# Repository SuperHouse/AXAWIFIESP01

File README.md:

AXA Electric Window Motor WiFi Controller (ESP-01)
===================================================
Copyright 2017 SuperHouse Automation Pty Ltd  www.superhouse.tv  

Add-in board for AXA domestic electric window mechanisms, to fit into
the battery compartment in place of the AA cells that are normally
installed. Uses an ESP8266 to connect to WiFi, and controls the AXA
window motor using LINbus.

More information is available on the project page at:

  http://www.superhouse.tv/axawifi

INSTALLATION
------------
The design is saved as an EAGLE project. EAGLE PCB design software is
available from www.cadsoftusa.com free for non-commercial use. To use
this project download it and place the directory containing these files
into the "eagle" directory on your computer. Then open EAGLE and
navigate to the projects listing.

DISTRIBUTION
------------
The specific terms of distribution of this project are governed by the
license referenced below.

LICENSE
-------
Licensed under the TAPR Open Hardware License (www.tapr.org/OHL).
The "license" folder within this repository also contains a copy of
this license in plain text format.

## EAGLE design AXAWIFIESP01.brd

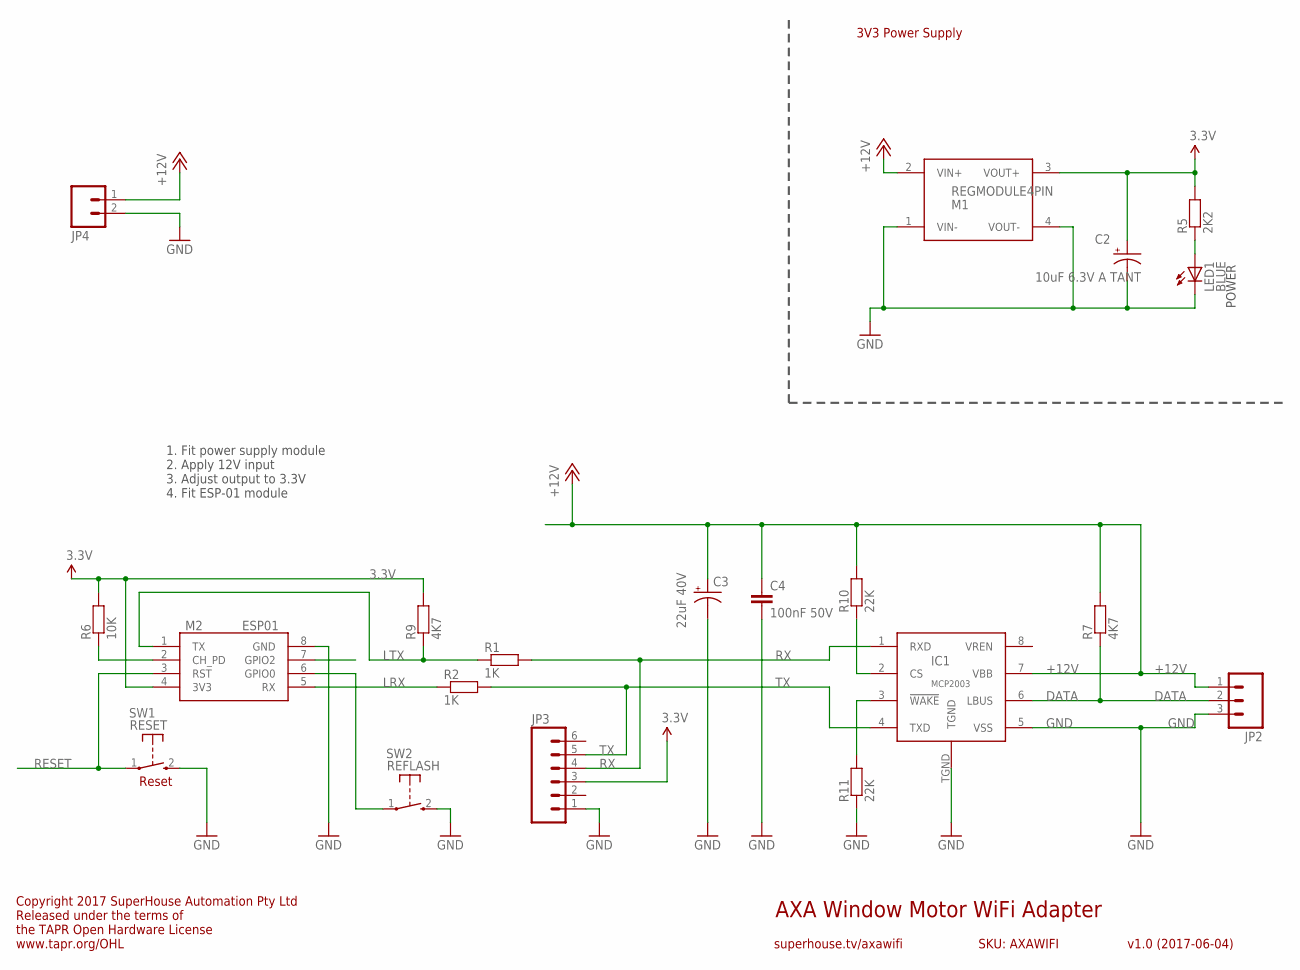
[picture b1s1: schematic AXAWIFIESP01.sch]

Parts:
C2: 10uF 6.3V A TANT; EIA3216
C3: 22uF 40V; PANASONIC_C
C4: 100nF 50V; C0603
IC1: MCP2003; SOIC8T
JP2: M03PTH; 1X03
JP3: M06SIP; 1X06
JP4: M02-SCREW-3.5MM; SCREWTERMINAL-3.5MM-2
LED1: BLUE; LED-0603
M1: REGMODULE4PIN
M2: ESP01
R1, R2: 1K; R0603
R5: 2K2; R0603
R6: 10K; R0603
R7, R9: 4K7; R0603
R10, R11: 22K; R0603
SW1: RESET; TACTILE_SMT_3X4X2
SW2: REFLASH; TACTILE_SMT_3X4X2

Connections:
3.3V: C2.A (+), JP3.3, M1.3 (VOUT+), M2.4 (3V3), R5.2, R6.2, R9.2
+12V: C3.+, C4.1, IC1.7 (VBB), JP2.1, JP4.1, M1.2 (VIN+), R7.2, R10.2
DATA: IC1.6 (LBUS), JP2.2, R7.1
GND: C2.C (-), C3.-, C4.2, IC1.5 (VSS), IC1.TGND, JP2.3, JP3.1, JP4.2, LED1.C, M1.1 (VIN-), M1.4 (VOUT-), M2.8 (GND), R11.1, SW1.2 (S), SW2.2 (S)
LRX: M2.5 (RX), R2.1
LTX: M2.1 (TX), R1.1, R9.1
unnamed: M2.6 (GPIO0), SW2.1
unnamed: M2.2 (CH_PD), R6.1
unnamed: IC1.2 (CS), R10.1
unnamed: IC1.3 (!WAKE), R11.2
unnamed: LED1.A, R5.1
RESET: M2.3 (RST), SW1.1
RX: IC1.1 (RXD), JP3.4, R1.2
TX: IC1.4 (TXD), JP3.5, R2.2

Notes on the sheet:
AXA Window Motor WiFi Adapter
v1.0 (2017-06-04)
superhouse.tv/axawifi
SKU: AXAWIFI
Reset
Copyright 2017 SuperHouse Automation Pty Ltd Released under the terms of the TAPR Open Hardware License www.tapr.org/OHL
POWER
3V3 Power Supply
1. Fit power supply module 2. Apply 12V input 3. Adjust output to 3.3V 4. Fit ESP-01 module

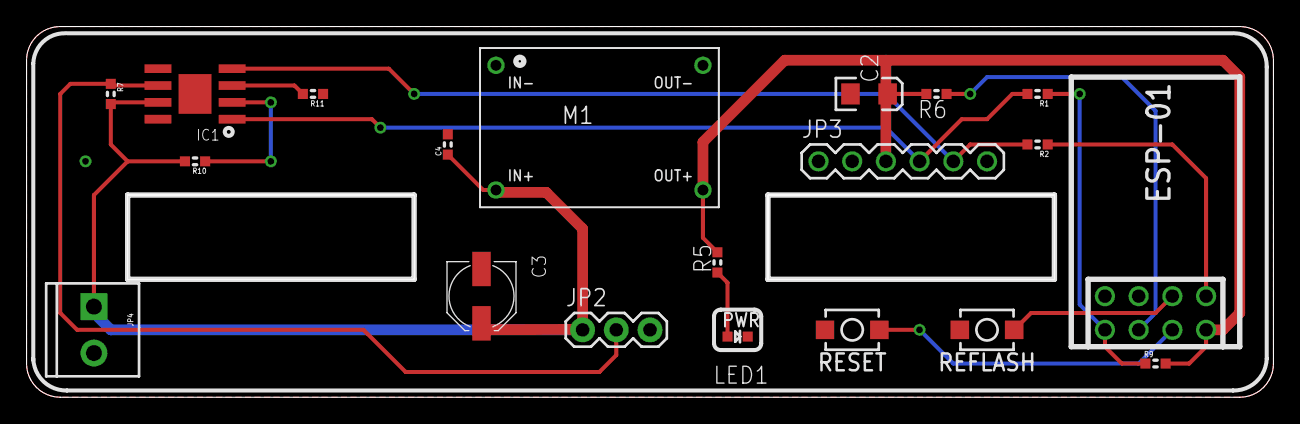
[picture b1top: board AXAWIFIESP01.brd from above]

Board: 2 copper layers, 94.0 x 27.9 mm, 20 parts (0 on the bottom side), 14 nets.

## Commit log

2018-03-22 Initial project import from June 2017
2020-05-27 Replace parts using SuperHouse library for 3D models

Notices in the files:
AXAWIFIESP01.brd:
(c) 2017 SuperHouse Automation Pty Ltd
Open Hardware License
